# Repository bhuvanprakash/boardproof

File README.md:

<p align="center">
  <br>
  <strong>BoardProof</strong><br>
  <sub>hardware CI starter v0.2</sub>
</p>

<p align="center">
  GitHub Actions for hardware designs.<br>
  Checks <em>reviewed</em> electrical and firmware rules against a real EasyEDA Pro netlist
  <strong>before</strong> PCB fabrication.
</p>

<p align="center">
  <a href="https://github.com/bhuvanprakash/boardproof">github.com/bhuvanprakash/boardproof</a>
</p>

| | |
| --- | --- |
| Version | 0.2.0 |
| License | MIT |
| Python | 3.10+ |
| Node | 20.9+ (Next.js UI) |
| UI | Next.js frontend + Python API |

Gemini may **propose** a constraint. It may never **enforce** one. That boundary is code, not a prompt. A green check means the configured rules passed. It is not a claim of electrical correctness, EMC compliance, or readiness to manufacture.

The demo uses a fictional MCU and sensor. It is **not** an ESP32 schematic or a manufacturing-ready circuit. No silicon pinouts or datasheet values are implied by the demo.

---

## Contents

1. [Start the web app](#start-the-web-app)
2. [Install and run the CLI demo](#install-and-run-the-cli-demo)
3. [What the broken demo catches](#what-the-broken-demo-catches)
4. [How a rule becomes enforceable](#how-a-rule-becomes-enforceable)
5. [Commands](#commands)
6. [Red team](#does-the-rule-set-actually-work-red-team)
7. [Revision gate](#revision-gate-not-a-backlog)
8. [Speed](#speed)
9. [Onboarding a real board](#onboarding-a-real-board)
10. [Gemini datasheet proposals](#optional-gemini-datasheet-proposals)
11. [Manufacturing Preflight Passport](#manufacturing-preflight-passport)
12. [Design and prove](#design-and-prove-generate-a-board-then-verify-the-file)
13. [Datasheet-driven layout](#datasheet-driven-layout-verification)
14. [Studio dashboard](#studio-run-it-from-the-dashboard)
15. [Demo surface](#demo-surface)
16. [Web app API](#web-app-api-details)
17. [Judges: 90 seconds](#demo-for-judges-90-seconds)
18. [Architecture](#architecture)
19. [Limits](#what-this-reads-and-what-it-does-not)

---

## Start the web app

Two processes. Leave both running.

| Process | Where | Port |
| --- | --- | --- |
| Backend | Python FastAPI (`boardproof-api`) | http://127.0.0.1:8193 |
| Frontend | Next.js app in `web/` | http://localhost:3000 |

### 1. Backend (Python API)

From the repository root:

```sh
python3 -m venv .venv
source .venv/bin/activate
python -m pip install -e '.[api]'
BOARDPROOF_ROOT=. BOARDPROOF_DIR=artifacts boardproof-api
```

- Health: http://127.0.0.1:8193/healthz
- Docs: http://127.0.0.1:8193/docs

| Variable | Default | What it does |
| --- | --- | --- |
| `BOARDPROOF_ROOT` | `.` | Repo / workspace root the API is allowed to read |
| `BOARDPROOF_DIR` | `<root>/artifacts` | Where reports, SVGs, and Gerbers are written |
| `BOARDPROOF_DATASHEETS_DIR` | `<root>/datasheets` | Pinned datasheet PDFs and their `registry.json` |
| `BOARDPROOF_API_HOST` | `127.0.0.1` | Bind address. Use `0.0.0.0` only with a token |
| `PORT` | `8193` | API port |
| `BOARDPROOF_API_TOKEN` | empty | Required if the API binds beyond localhost |
| `BOARDPROOF_WEB_ORIGINS` | `http://localhost:3000,http://127.0.0.1:3000` | Allowed browser origins |
| `GEMINI_API_KEY` | unset | Optional. Datasheet / brief / photo import |

The API is one local workspace. It is not a multi-user service.

### 2. Frontend (Next.js)

Keep the backend running. In a **second** terminal:

```sh
cd web
npm ci
cp .env.example .env.local
npm run dev
```

Open http://localhost:3000. Next.js proxies `/api/*` to the Python backend, so the browser never holds `BOARDPROOF_API_TOKEN`.

The sign-in screen is a local demo gate: it saves the entered email in the current browser tab. Password accounts, teams, and access roles are not implemented.

| Path | Page |
| --- | --- |
| `/login` | Local demo sign-in |
| `/` | Overview workbench |
| `/dashboard` | Runs and evidence |
| `/product` | Product notes |
| `/how-it-works` | Trust chain and commands |

`web/.env.local`:

```
BOARDPROOF_API_URL=http://127.0.0.1:8193
BOARDPROOF_API_TOKEN=
```

If you set a token on the backend, put the **same** value in `web/.env.local`. Do not put it in client code.

| Script | What it does |
| --- | --- |
| `npm run dev` | Next.js dev server (port 3000) |
| `npm run build` | Production build |
| `npm start` | Serve the production build (run `build` first) |
| `npm run typecheck` | TypeScript check |

On Overview: **Demo 1** opens the Jeden Uno in the 2D / 3D viewers. **Import demo board** loads its KiCad layout so you can export Gerbers. **Demo 2** checks TMP102 Rev B (broken) and offers the Rev C (fixed) comparison. Datasheet lookup is opt-in.

CLI-only checks (no browser) are in the next section. Studio / `boardproof serve` on port 8080 is a separate stdlib dashboard, not the Next.js app.

---

## Install and run the CLI demo

Python 3.10+:

```sh
python3 -m venv .venv
source .venv/bin/activate
python -m pip install -e .
python -m unittest discover -s tests -v

# Clean board; exits 0
boardproof check --config examples/demo/boardproof.clean.json --html artifacts/clean.html --json artifacts/clean.json

# Same board with a vetted, cited rule pack
boardproof check --config examples/demo/boardproof.pack.clean.json --html artifacts/pack-clean.html

# Deliberately broken board, with grounded explanations; exits 1
boardproof check --config examples/demo/boardproof.pack.json --explain --engine offline \
  --html artifacts/broken.html --json artifacts/broken.json
```

Open `artifacts/broken.html` in a browser. Every finding carries the datasheet page, the quoted text, the pack id and the human who vetted it. GitHub Actions CI is at `.github/workflows/boardproof.yml`. It runs on pushes and pull requests and uploads artifacts.

| Exit | Meaning |
| ---: | --- |
| **0** | Configured rules passed |
| **1** | Findings (at least one error) |
| **2** | Cannot verify (missing/malformed input, or a pack is still `proposed`) |

A missing or malformed input produces exit code **2**, never a false passing check. Unverifiable configured checks are errors by default; downgrade one rule with `"severity": "warning"`.

---

## What the broken demo catches

| Rule | Demo issue | Proof source |
| --- | --- | --- |
| `pin_net` | U1 VDD accidentally connected to `5V` rather than `3V3` | `.enet` connection and reviewed expected net |
| `max_voltage` | 5.0 V assigned to a simulated 3.6 V maximum VDD input | Explicit `net_voltages` and reviewed limit |
| `connected` | Sensor ground pin left disconnected | `.enet` |
| `resistor_between` | SDA pull-up resistor missing | `.enet` + reviewed I2C requirement |
| `firmware_gpio` | LED connects to GPIO4, firmware defines `LED_PIN=5` | `.enet` pin name + simple numeric C `#define` |

A voltage is not inferred from a net's name alone. It must be declared in `net_voltages`. Ranges are **not** derived from the model by default. Every asserted limit should be verified against an authoritative datasheet for the correct part number, package, and conditions.

---

## How a rule becomes enforceable

```mermaid
flowchart TD
  PDF["datasheet.pdf"] --> Infer["boardproof infer"]
  Infer --> Propose["*.propose.json  -  proposed, untrusted"]
  Propose --> Vet["boardproof vet --reviewer"]
  Vet --> Pack["packs/*.json  -  vetted, cited, reviewed_by"]
  ENET["board.enet + firmware.h"] --> Check["boardproof check"]
  Pack --> Check
  Check --> Report["report.html / report.json"]
  Check --> Explain["boardproof check --explain  -  read-only prose"]
```

Three invariants are enforced structurally:

1. **No citation, no limit.** A rule asserting `max_v`, `min_v`, `min_ohms` or `max_ohms` without a page number and an exact quote is rejected at load time.
2. **No reviewer, no enforcement.** `check` against a `proposed` pack exits **2** (cannot verify), never **0** (clean).
3. **The model cannot widen the evidence base.** Explanations citing a page BoardProof did not supply are dropped, and an explanation can never change a verdict. There is a test that asserts exactly that.

Offline (no API key):

```sh
boardproof infer --pdf examples/demo/demo-mcu-SIMULATED.pdf --component U1 \
  --netlist examples/demo/broken.enet --out packs/u1.propose.json \
  --engine offline --fixture examples/demo/fixtures/demo-mcu.facts.json

boardproof check --config examples/demo/boardproof.pack.json   # exits 2: pack is not vetted
boardproof vet --proposal packs/u1.propose.json --reviewer "Your Name"
boardproof check --config examples/demo/boardproof.pack.json --explain --html artifacts/pack.html
```

---

## Commands

| Command | Purpose | Network |
| --- | --- | --- |
| `boardproof check` | Enforce vetted packs + inline rules. Exit 0 pass / 1 findings / 2 cannot verify | no |
| `boardproof infer` | Read a datasheet PDF, propose cited constraints, diff against the current pack | Gemini (or `--engine offline --fixture`) |
| `boardproof vet` | Human gate: attach a reviewer name, flip `proposed` to `vetted` | no |
| `boardproof explain` | Grounded explanation of current findings | Gemini (or offline) |
| `boardproof redteam` | Inject faults into a known-good design and score the rule set | no |
| `boardproof diff` | Block a PR only on **newly introduced** violations | no |
| `boardproof bench` | Throughput on a synthetic board; fails a CI perf budget | no |
| `boardproof init` | Draft a `boardproof.json` from a fresh netlist export | no |
| `boardproof passport` | Manufacturing Preflight Passport (printable HTML + hashed JSON) | no |
| `boardproof dashboard` | One page linking every artifact | no |
| `boardproof serve` | Serve the artifacts (Cloud Run compatible, stdlib only) | no |
| `boardproof studio` | Dashboard control room: prove, check, design, passport | no |
| `boardproof design` | Verified schematic to editable `.kicad_pcb` + SVG | no |
| `boardproof pcb-check` | Re-read the board from disk and prove it (KiCad DRC) | no |
| `boardproof pcb-redteam` | Mutate the board, score the layout verifier | no |
| `boardproof prove` | The whole journey in one run, exit code and all | optional |
| `boardproof datasheet` | Fetch, hash, and register a datasheet PDF | optional |
| `boardproof package` | Infer / vet mechanical package specs from a drawing | Gemini (or offline) |
| `boardproof-api` | FastAPI for the web app (`pip install -e '.[api]'`) | no |

---

## Does the rule set actually work? (red team)

`boardproof redteam` mutates a known-good design in ways a real engineer could: swap a supply rail, float a ground, delete a pull-up, drift a resistor value 100x, shift a firmware pin. Faults are derived from the rules themselves, so every targeted fault is relevant by construction.

```
RED TEAM  8/8 targeted faults caught (100%)  ·  1 blind spot(s)  ·  1 unverifiable from a netlist
  [PASS] supply_swap      U1.1 (VDD) reconnected to 5V instead of 3V3
         caught by MAX_VOLTAGE
  [GAP ] net_typo         one-character net rename strands U1.4 (GPIO5, DEBUG)
         nothing constrains this yet
  [SKIP] not_representable symbol pin order disagrees with the physical footprint
         a .enet netlist carries pin numbers, not footprint pads - needs PCB-level data
```

Blind spots are reported with the rule that would close them, and `--min-score 1.0` turns that into a CI gate: a rule that cannot be mutated is decoration.

---

## Revision gate, not a backlog

`boardproof diff --base base.json --head pr.json` separates **introduced** from **pre-existing** violations, so a hardware PR is blocked by the regression it adds, not by history:

```
BoardProof revision diff: 0 error(s) -> 5 error(s)  (passed -> failed)
  [NEW  ] MAX_VOLTAGE: U1.1 on 5V has declared 5 V; allowed 2.7 to 3.6 V  (regression)
  VERDICT: this revision introduces new hardware violations - blocked
```

---

## Speed

The `resistor_between` check used to scan every component for every rule, O(rules x components). `boardproof/index.py` builds a net-pair table once per design, so it is O(components + rules). Net and pin lookups are cached on the design; rule packs and firmware files are validated once per (path, mtime, size) and handed out as private copies.

```
$ boardproof bench --components 20000 --rules 4000
BoardProof bench  20,000 components · 40,002 nets · 4,000 rules (best of 2)
  netlist parse     156.91 ms
  checks              9.12 ms   (438,833 rules/s)
```

CI enforces a budget (`--max-checks-ms`) so this cannot silently regress.

---

## Onboarding a real board

```sh
boardproof init --netlist board.enet --firmware src/pins.h   # drafts rules
boardproof check --config boardproof.json                    # exit 0: warnings only
```

`init` emits every rule as `severity: "warning"` with a `DRAFT` note and tells you which numbers it guessed. A generated rule **cannot** block a build. Promotion to `error` is a human edit. That keeps the same invariant as the AI path: nothing invented is ever enforced.

### Exporting from EasyEDA Pro

1. Open the schematic/project in **EasyEDA Pro**.
2. Use **File -> Export -> Export Netlist**.
3. Select **EasyEDA Pro `.enet`** and export the whole project if appropriate.
4. Commit the export and your `boardproof.json` to the repo.
5. Re-export whenever the schematic changes. CI cannot detect stale exports unless you enforce that workflow separately.

For Standard Edition, the current MVP requires a converter from its compressed schematic shape format. Do not rename a Standard `.json` to `.enet`; the tool will reject it. [EasyEDA Pro export documentation](https://prodocs.easyeda.com/en/schematic/export-netlist/).

### Add checks for your board

Create `boardproof.json` next to the export:

```json
{
  "schema_version": 1,
  "netlist": "board.enet",
  "firmware": "firmware/pins.h",
  "net_voltages": {"3V3": 3.3, "5V": 5.0, "GND": 0.0},
  "rules": [
    {"id": "mcu-vdd", "type": "pin_net", "component": "U1", "pin": "1", "net": "3V3"},
    {"id": "mcu-vdd-limit", "type": "max_voltage", "component": "U1", "pin": "1", "min_v": 2.7, "max_v": 3.6},
    {"id": "mcu-ground", "type": "connected", "component": "U1", "pin": "2"},
    {"id": "i2c-sda-pullup", "type": "resistor_between", "net_a": "I2C_SDA", "net_b": "3V3", "min_ohms": 1000, "max_ohms": 10000},
    {"id": "firmware-led-pin", "type": "firmware_gpio", "define": "LED_PIN", "component": "U1", "net": "LED_STATUS"}
  ]
}
```

All relative paths are resolved against the config file. `firmware_gpio` compares a simple numerical `#define` with the MCU pin's name (default `GPIO(\\d+)` or `IO(\\d+)`, or customize `pin_label_regex`). It is **not** a real compiler, does not follow `#include`, and does not understand alternate pin multiplexing or module pin numbering unless explicitly modeled.

---

## Optional Gemini datasheet proposals

```sh
pip install -e '.[ai]'
export GEMINI_API_KEY='your-key'    # never commit this secret
boardproof infer --pdf datasheets/part.pdf --component U1 --out packs/U1.propose.json
boardproof vet --proposal packs/U1.propose.json --reviewer "Your Name"   # after you check the pages
```

Review cited text, printed page numbers, exact package variant, and operating versus absolute-maximum ratings manually. **Do not import proposals directly into a blocking CI ruleset without verifying them.** This optional API integration was written against the Google Gen AI SDK but has **not** been live-tested with an API key in this environment.

---

## Manufacturing Preflight Passport

`boardproof passport` produces a printable one-pager (plus hashed JSON) that answers three questions in order:

1. what failed
2. what was actually verified and by whom
3. what remains unverified

The last section is mandatory. A PASS is only as wide as its scope list. Each passport carries a `passport_hash` over the netlist hash, the packs, the reviewers and the findings, so two revisions can be compared without trusting either file.

```sh
boardproof passport --config boardproof.json --revision "Rev B" \
  --redteam artifacts/redteam.json --base artifacts/previous.json \
  --out artifacts/passport.html --json artifacts/passport.json
```

---

## Design and prove: generate a board, then verify the file

```sh
boardproof design   --config boardproof.json --outline 44x48mm --route --output board.kicad_pcb
boardproof pcb-check --board board.kicad_pcb --config boardproof.json --require-routing
```

`design` refuses to run while the schematic still has critical violations, so a bad circuit never becomes a board file. `pcb-check` then **re-reads the file from disk** and proves, independently of the generator:

- pad-to-net assignment matches the verified netlist (the classic symbol-vs-pad trap)
- every netlist component has exactly one footprint
- every multi-pad net is joined by real copper
- copper clearance, board-outline containment, decoupling distance
- KiCad DRC, when `kicad-cli` is installed

```
DESIGN: 5 footprints, 14 pads on a 44x48 mm board -> board.kicad_pcb
PCB CHECK PASSED: 5 footprints, 14 pads, 5/5 nets fully connected, 37 tracks, 28 vias
  KiCad DRC: 5 violation(s), 0 unconnected, 0 parity
```

Honest scope, stated in the artifact itself: land patterns are **approximate** (replace with fab-approved footprints), and routing is only attempted with `--route`. Without it you get a verified placement and pad mapping, reported as notices, not as a pass.

### One command for the whole journey

```sh
boardproof prove --config boardproof.json --outline 44x48mm --revision "Rev A"
```

```
BOARDPROOF PROVE
  [PASS ] check            0 error(s)
  [DONE ] design           5 footprints, 14 pads
  [PASS ] pcb-check        5/5 nets connected, 0 error(s)
  [PASS ] red-team         8/8 targeted faults caught
  [PASS ] layout-red-team  5/5 layout faults caught
  [CLEAR] passport         0 critical, 5 unverified
```

A broken circuit stops at step two (`design` refuses), so the pipeline cannot produce a manufacturing artifact from a board that failed review:

```
  [FAIL ] check     5 error(s)
  [STOP ] design    critical schematic violations must be fixed before a board is generated
  [BLOCK] passport  5 critical, 5 unverified
```

---

## Datasheet-driven layout verification

The strongest link in the chain: the layout is checked against the part's own drawing.

```sh
boardproof datasheet --part TMP102AIDRLR              # fetch, hash, register the PDF
boardproof package   infer --pdf datasheets/tmp102aidrlr.pdf --part TMP102AIDRLR \
                     --out packs/packages/tmp102.propose.json --engine gemini
boardproof package   vet   --proposal packs/packages/tmp102.propose.json --reviewer "Your Name"
```

`infer` reads the mechanical drawing and returns pin count, pad pitch, body size and lead width **with the page and the quoted dimension string**. `vet` is the human gate, exactly as for rule packs. The board config then references the spec:

```json
{ "packages": ["packs/packages/tmp102.json"],
  "net_currents": { "3V3": 0.05 },
  "copper_oz": 1.0 }
```

This closed two entries in the passport's "not verified" list:

```
+ land pattern vs datasheet SOT-5X3 (DRL) (p.30)
+ track current capacity (IPC-2221, 1 oz copper)
```

And it immediately caught a real error in our own library:

```
[ERROR] LAND_PATTERN_MISMATCH: U1 (SOT563-6): library pitch 0.65 mm vs datasheet 0.5 mm
        (SOT-5X3 (DRL) drawing, p.30)
```

The library had been guessed at 0.65 mm; TI's DRL0006A drawing says `4X 0.5`. Correcting it then exposed a second, deeper issue: a 0.6 mm via cannot fan out from a 0.5 mm-pitch row, so the router now **refuses to emit copper** rather than ship a short, and the pipeline falls back to a verified placement board that says so.

---

## Studio: run it from the dashboard

```sh
boardproof studio --dir artifacts        # http://localhost:8080
```

The dashboard becomes a control room: pick a `boardproof.json`, press **Prove it** and the whole journey runs in-process, streams its log into the page, rewrites the artifact cards and reloads. Every action is a fixed function from this package. No shell, no arbitrary paths: `prove`, `check`, `design`, `pcb`, `redteam`, `passport`, `refresh`. Configs are discovered inside `--root`, and a request naming a path outside it is refused.

Same process serves Cloud Run (`/healthz`, `PORT`). Opened as a plain file, the buttons are inert and say so. There is no hidden network dependency.

### The board is on the dashboard

`artifacts/*.svg` is rendered inline, on a grid backdrop, next to the facts that matter: footprints, pads, board size, copper, the `pcb-check` verdict and the checks that passed, including *land pattern vs datasheet* and *IPC-2221 current capacity*. When the router declined, the panel says **routing not attempted**. It never shows a green board that was not verified.

---

## Demo surface

```sh
boardproof dashboard --dir artifacts   # artifacts/index.html
boardproof serve --dir artifacts       # http://localhost:8080 (+ /healthz for Cloud Run)
```

`serve` is the stdlib HTTP server with a health endpoint, so the same artifacts run locally and on Cloud Run with `--port $PORT`. `docker build . && docker run -p 8080:8080 <image>` produces a container whose dashboard is already populated.

---

## Web app API details

Start steps, env vars, and Next.js scripts are under [Start the web app](#start-the-web-app).

The FastAPI backend exposes the same Python onboarding and check engine the CLI uses.

| Method | Path |
| --- | --- |
| `GET` | `/healthz` |
| `GET` | `/api/state` |
| `GET` | `/api/previews` | Schematic and datasheet previews with size and mtime |
| `GET` | `/api/datasheets` | Datasheet registry: hash, source, cited page per part |
| `POST` | `/api/datasheets/fetch` | Pin one part's PDF and record its SHA-256 |
| `POST` | `/api/datasheets/verify` | Re-hash one stored datasheet against the registry |
| `GET` | `/api/datasheets/pdf/{part}` | Download a pinned datasheet (slugified, traversal-guarded) |
| `GET` | `/api/artifacts/{filename}` |
| `POST` | `/api/upload` |
| `POST` | `/api/run` |

`/api/datasheets/fetch` takes `part`, an optional direct `url`, and `refresh`. It only guesses a URL for part prefixes with a known vendor pattern; anything else is refused with a 422 instead of a wrong download. Files over 64 MB or without a `%PDF` header are never stored. `/api/datasheets/verify` re-computes the hash and reports drift — it never repairs it.

Interactive API docs are at `/docs`. Upload JSON accepts `filename` plus `content_b64` (base64) or UTF-8 `content`, and optional `kind`, `brief`, `config_path`, and `fetch_datasheets` (false by default). Firmware source (`.h`, `.ino`, `.c`, `.cc`, `.cpp`) can be attached to an existing BoardProof configuration. The current firmware check reads simple numeric `#define` values referenced by `firmware_gpio` rules; unsupported macros remain unknown. Checks keep BoardProof's existing exit-code meaning: a completed check with findings returns its result, while invalid input/configuration is an HTTP 422.

For an external bind, set `BOARDPROOF_API_TOKEN`, `BOARDPROOF_API_HOST=0.0.0.0`, and `BOARDPROOF_WEB_ORIGINS` to the exact frontend origin. Keep the bearer token in `web/.env.local` on the Next.js server; do not expose it in browser code.

The Next.js app in `web/` proxies those routes server-side to `BOARDPROOF_API_URL`. Import a netlist, firmware source, or KiCad board, or select an example configuration and run a check. Use the top navigation and **Tools** menu to review runs, rules, compatibility, 2D / 3D previews, and evidence. The web app reads previews from `BOARDPROOF_DIR` through the API. Datasheet lookup is opt-in, and importing a brief, photo, or schematic uses Gemini when configured.

The **Schematic** view lists every sheet drawn from the verified netlist with zoom, size, timestamp, and download/open links, and offers **Redraw from netlist** when none exists. The **Datasheets** view renders the registry as per-part cards — source host, pin time, size, truncated SHA-256 with copy, a **Verify hash** action that re-hashes the file on demand, and a thumbnail of the cited page — plus a form to fetch a part by number (or direct PDF URL) and a gallery of the rendered pages with zoom.

On Overview, **Demo 1** opens the Arduino-compatible Jeden Uno in the 2D and 3D viewers. Select **Import demo board** to bring the KiCad layout into your workspace and export Gerbers. **Demo 2** checks the faulty TMP102 Rev B and runs the corrected Rev C through board generation and verification. Use the board selector to switch layouts.

---

## Demo for judges: 90 seconds

1. Open the green `artifacts/clean.html` report.
2. Switch to `artifacts/broken.html`: five precise cross-layer failures, not generic AI advice.
3. Show `firmware_good.h` to `firmware_broken.h`, where `LED_PIN` changed from 4 to 5; GitHub Actions blocks the PR.
4. Explain that Gemini can convert datasheets into *reviewable candidate rules*. Deterministic checks, not AI opinions, decide whether CI fails.

---

## Architecture

```mermaid
flowchart LR
  ENET["EasyEDA Pro .enet"] --> IR["Normalized pin / net graph"]
  FW["Firmware C defines"] --> IR
  PACK["Reviewed rule JSON"] --> IR
  IR --> ENG["Deterministic verification"]
  ENG --> OUT["JSON + HTML report + GitHub annotations"]
  PDF["PDF datasheet"] --> GEM["Gemini proposal - optional"]
  GEM --> HUM["Human review"]
  HUM --> PACK
```

---

## What this reads, and what it does not

- **Implemented:** EasyEDA **Pro** `.enet` JSON, whose `components.*.pinInfoMap` contains pin numbers, names, and nets. [Official specification](https://github.com/easyeda/easyeda-netlist-format/blob/main/easyeda-pro-netlist-format-en.md).
- **Not implemented:** EasyEDA **Standard** `shape`-compressed JSON; Pro `.zip` project files; Allegro and PADS exports; PCB DRC as a replacement for KiCad; schematic ERC; electrical simulation; arbitrary C/C++ firmware analysis.
- **Offline checks:** require explicit, engineering-reviewed JSON rules. A failing critical rule produces exit code **1**. A missing or malformed input produces exit code **2**, never a false passing check.
- **AI (optional):** Gemini extracts *candidate* datasheet pin information from a PDF, with cited text/page and uncertainty. Output is **NOT** imported automatically as blocking rules. Human review is mandatory.

A green BoardProof check only means **the configured rules passed**. Continue to run native EasyEDA ERC/DRC, component review, appropriate simulation and hardware validation.

**Next technical milestones:** real EasyEDA Pro sample fixture compatibility; Standard Edition adapter; board-specific firmware parsers; electrical rules for shared-net drivers and power domains; bill-of-materials consistency; PR commenting; measured detection rates on deliberately fault-injected real boards.

---

License: MIT. See [`LICENSE`](LICENSE).

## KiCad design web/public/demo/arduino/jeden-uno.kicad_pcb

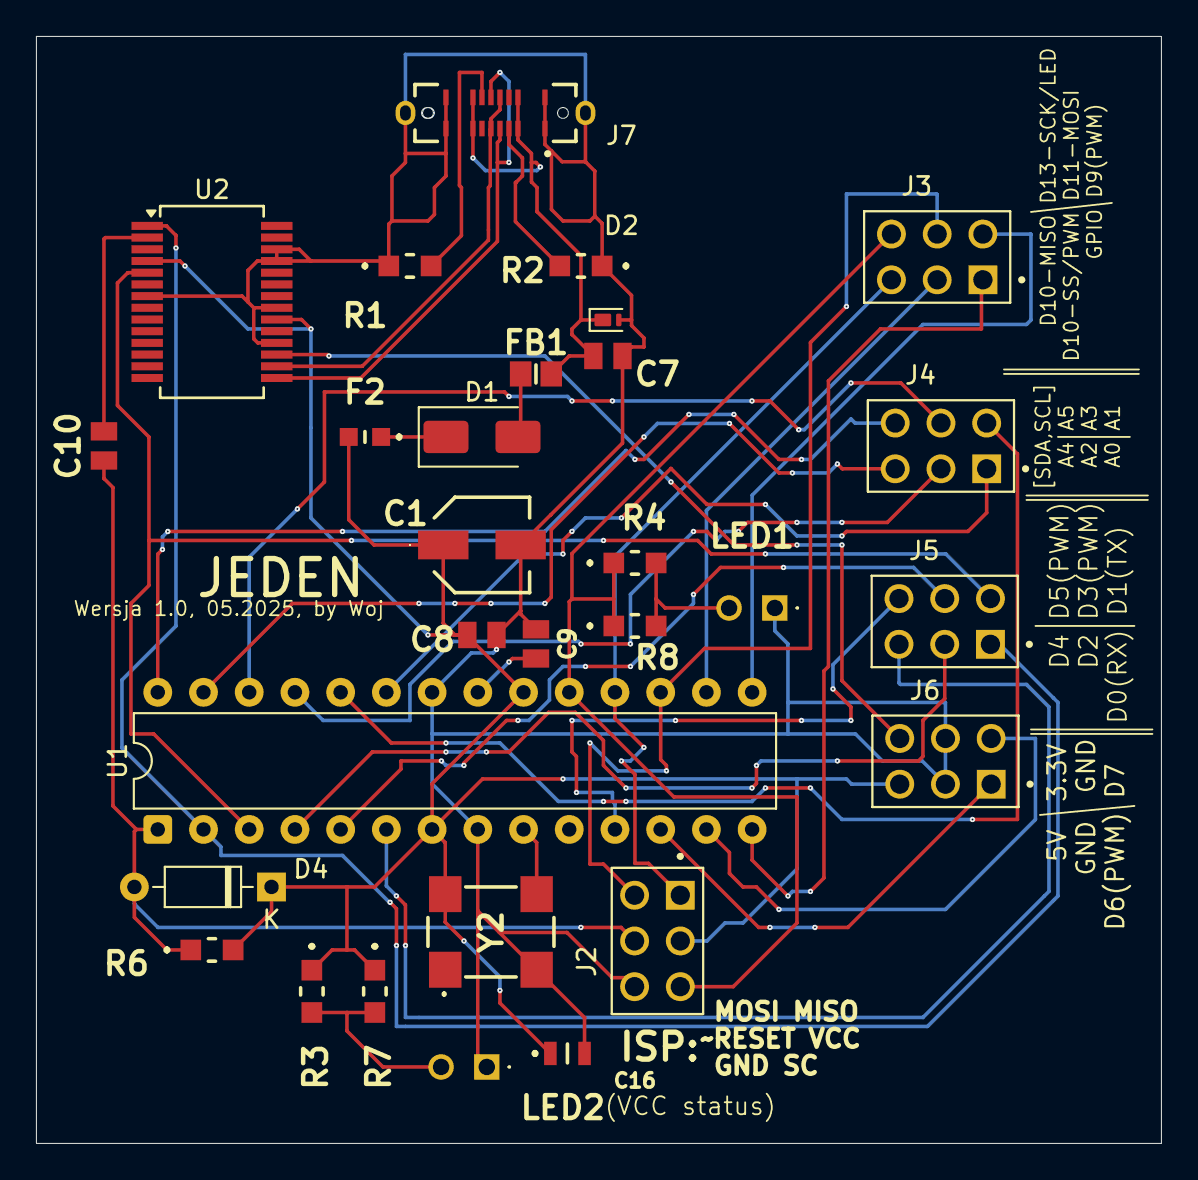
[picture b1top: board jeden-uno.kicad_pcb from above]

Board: 2 copper layers, 62.5 x 61.5 mm, 29 parts (0 on the bottom side), 36 nets.

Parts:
C1: EEE-1CA100NR; EEE0GA101SR
C7, C8, C9, C10: KAM21BR71H104JT; CAPC2012X94N
C16: GCM21B5G1H103FA16L; GCM21
D1: SS14; D_SMA
D2: PTVS5V0Z1USKP; Nexperia_DSN1608-2_1.6x0.8mm
D4: 1N4148; D_DO-35_SOD27_P7.62mm_Horizontal
F2: 0603L050SLYR
FB1: 742792040; BEADC2012X110N
J2, J3, J4, J5, J6: PPPC032LFBN-RC; SULLINS_PPPC032LFBN-RC
J7: USB4235-03-C_REVA; GCT_USB4235-03-C_REVA
LED1, LED2: C4SMM-BJY-CN3Q2352; C4SMMBJYCN3Q2352
R1, R2, R3, R4, R6, R7, R8: ERA-6ARW512V; ERA6AEB101V
U1: ATmega328-P; DIP-28_W7.62mm
U2: FT232RL; SSOP-28_5.3x10.2mm_P0.65mm
Y2: XO57CRECNA16M

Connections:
GND: C1.2 (-), C7.1, C8.1, C9.1, C16.2, D2.2 (A), J2.6, J6.3, J6.4, J7.A1 (GND_A), J7.A12 (GND_A), J7.B1 (GND_B), J7.B12 (GND_B), J7.SH1 (SHIELD), J7.SH2 (SHIELD), LED1.1 (K), LED2.1 (K), R1.1, R2.1, U1.8 (GND), U1.22 (GND), U2.7 (GND), U2.18 (GND), U2.21 (GND), U2.25 (AGND), U2.26 (TEST), Y2.2 (GND)
unnamed: C1.1 (+), C8.2, C16.1, D4.1 (K), F2.2, J2.3, J6.5, R3.1, R6.2, R7.1, U1.7 (VCC), U1.20 (AVCC), U2.4 (VCCIO), U2.20 (VCC), Y2.4 (VDD)
unnamed: D1.2 (A), FB1.2
unnamed: D1.1 (K), F2.1
unnamed: C10.1, D4.2 (A), J2.4, R6.1, U1.1 (~RESET/PC6)
unnamed: J7.A5 (CC1), R2.2
unnamed: J7.B5 (CC2), R1.2
unnamed: J7.A7 (DN1), J7.B7 (DN2), U2.16 (USBD-)
unnamed: J7.A6 (DP1), J7.B6 (DP2), U2.15 (USBD+)
unnamed: LED1.2 (A), R4.2, R8.2
unnamed: LED2.2 (A), R3.2, R7.2
unnamed: C9.2, U1.21 (AREF)
unnamed: J3.1, U1.14 (PB0)
unnamed: J3.2, U1.15 (PB1)
unnamed: J3.3, U1.16 (PB2)
unnamed: J2.2, J3.4, U1.17 (PB3)
unnamed: J2.1, J3.5, U1.18 (PB4)
unnamed: J2.5, J3.6, R4.1, R8.1, U1.19 (PB5)
unnamed: J4.1, U1.23 (PC0)
unnamed: J4.2, U1.24 (PC1)
unnamed: J4.3, U1.25 (PC2)
unnamed: J4.4, U1.26 (PC3)
unnamed: J4.5, U1.27 (PC4)
unnamed: J4.6, U1.28 (PC5)
unnamed: J5.1, U1.2 (PD0), U2.1 (TXD)
unnamed: J5.2, U1.3 (PD1), U2.5 (RXD)
unnamed: J5.3, U1.4 (PD2)
unnamed: J5.4, U1.5 (PD3)
unnamed: J5.5, U1.6 (PD4)
unnamed: J5.6, U1.11 (PD5)
unnamed: J6.1, U1.12 (PD6)
unnamed: J6.2, U1.13 (PD7)
unnamed: U1.9 (XTAL1/PB6), Y2.3 (OUTPUT)
unnamed: J6.6, U2.17 (3V3OUT)
unnamed: C10.2, U2.2 (DTR)
VCC: C7.2, D2.1 (K), FB1.1, J7.A4 (VBUS_A), J7.A9 (VBUS_A), J7.B4 (VBUS_B), J7.B9 (VBUS_B)
